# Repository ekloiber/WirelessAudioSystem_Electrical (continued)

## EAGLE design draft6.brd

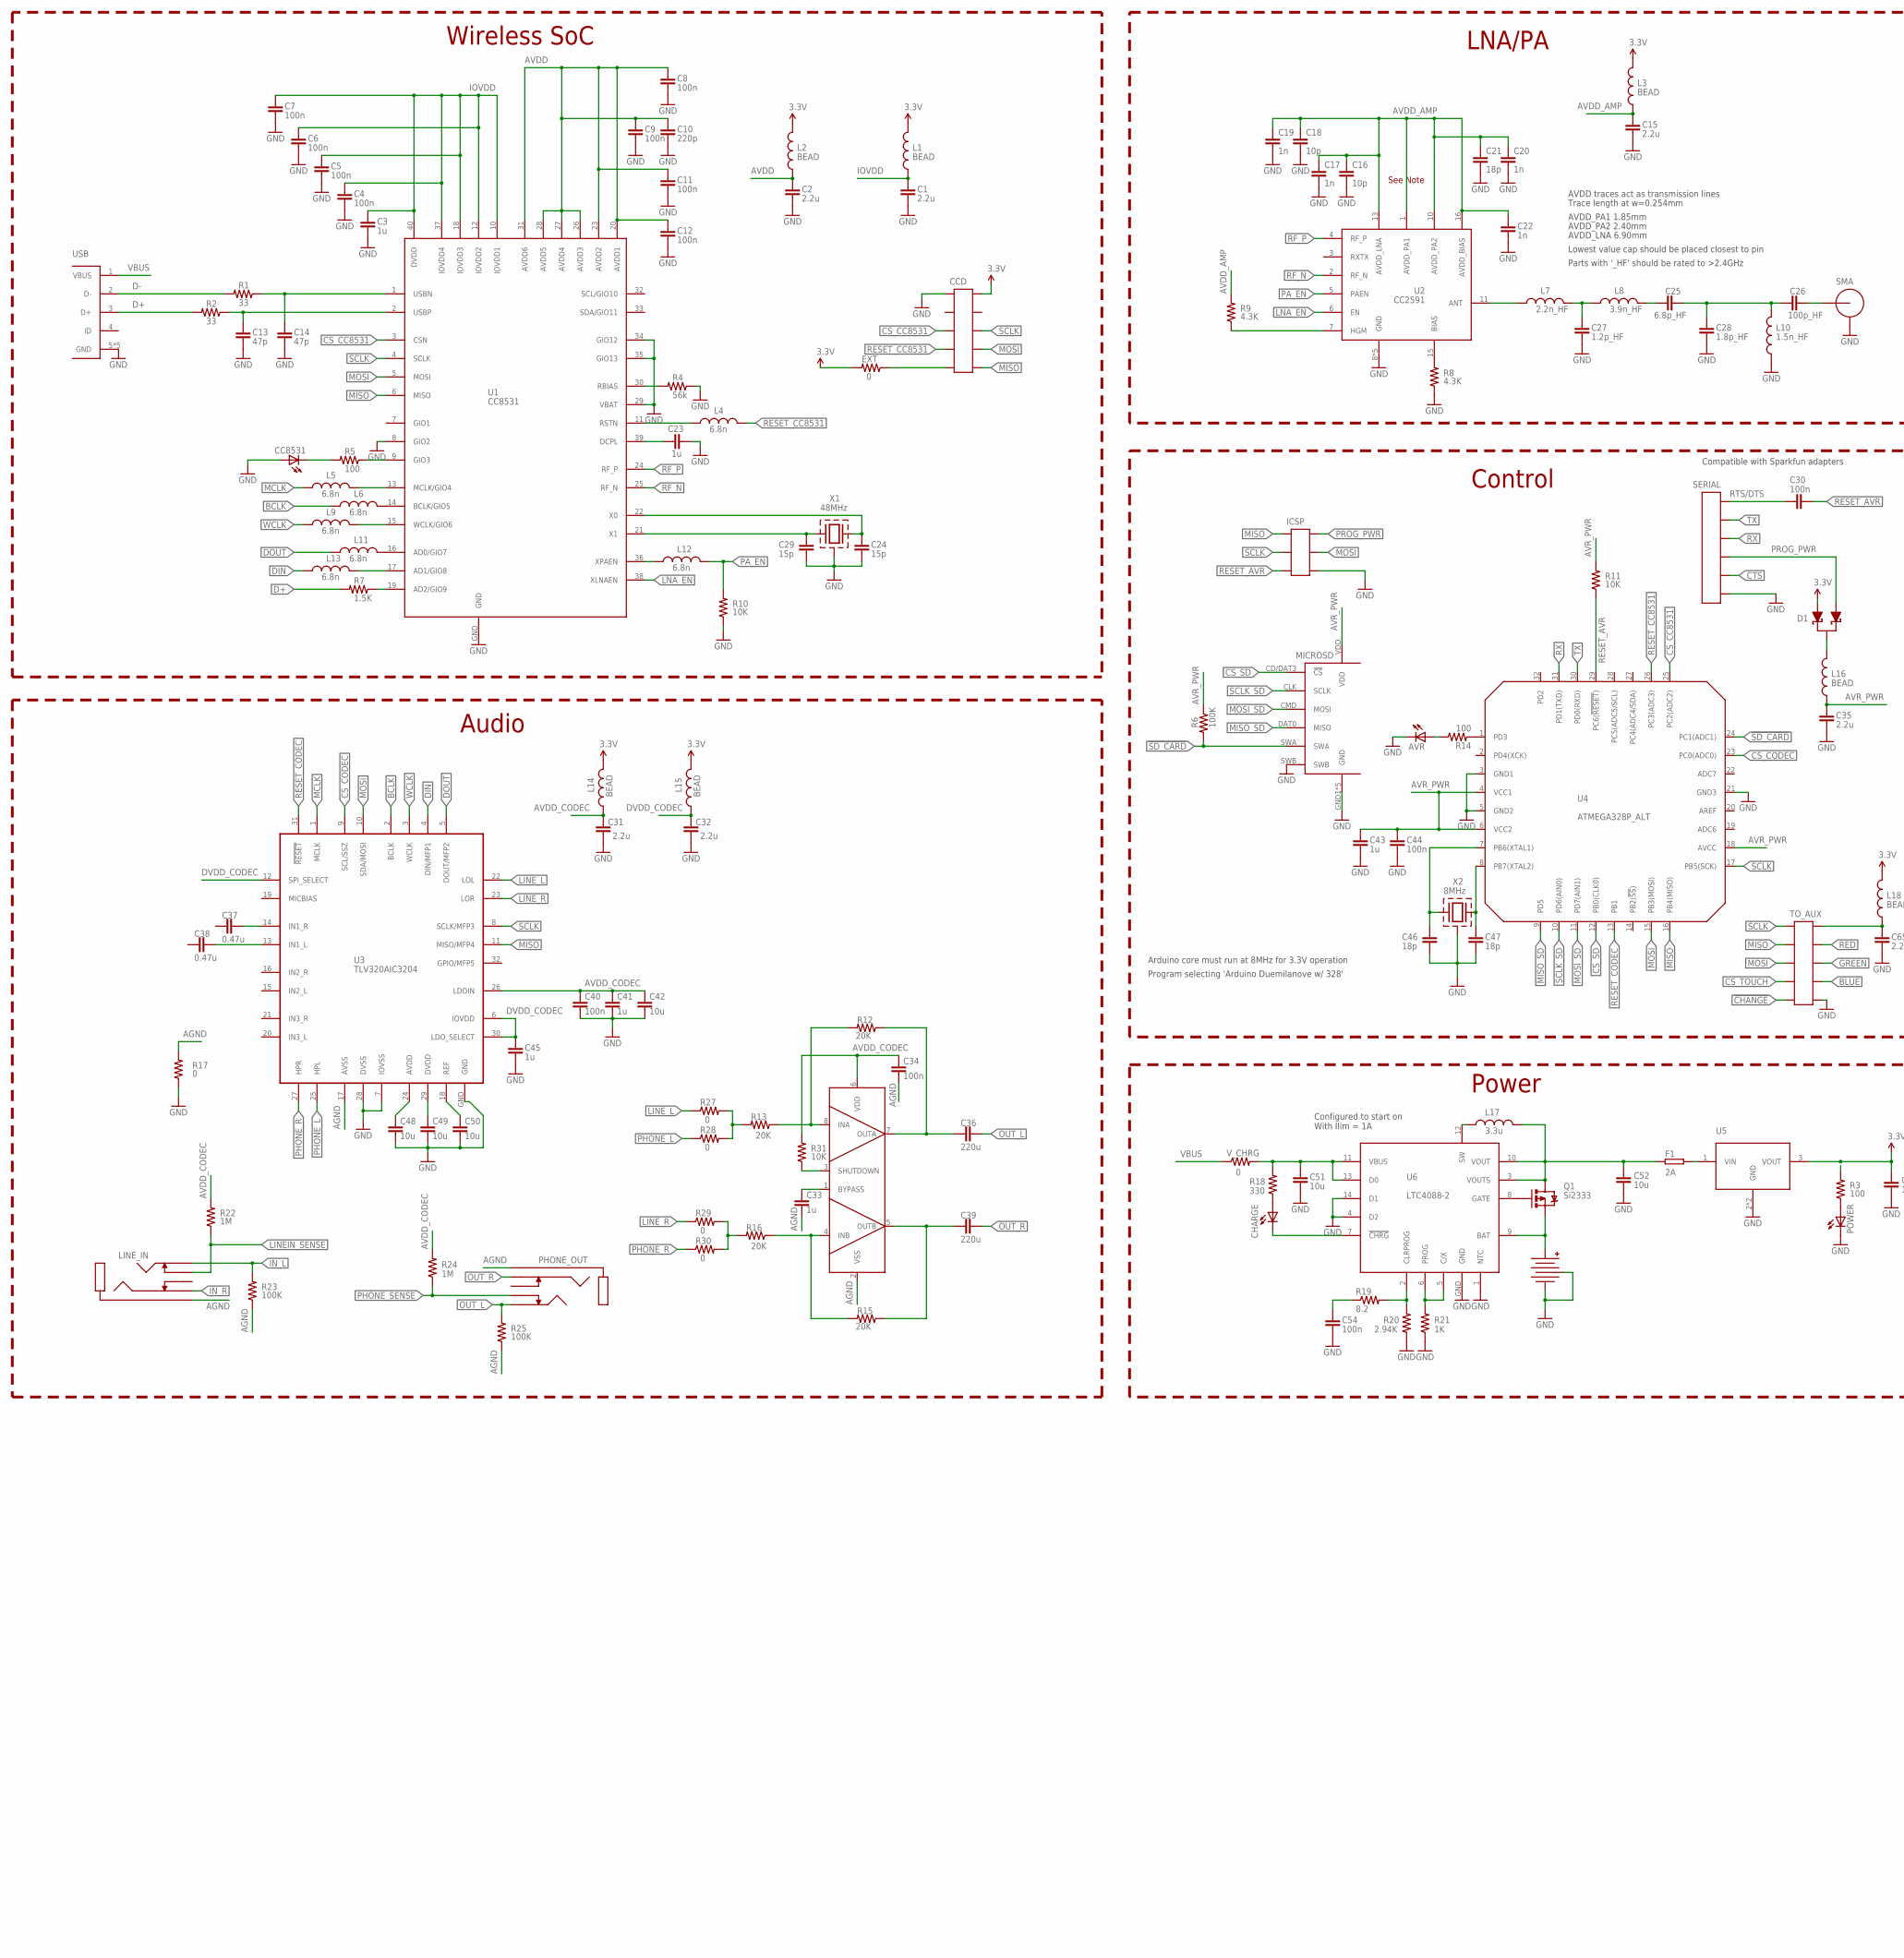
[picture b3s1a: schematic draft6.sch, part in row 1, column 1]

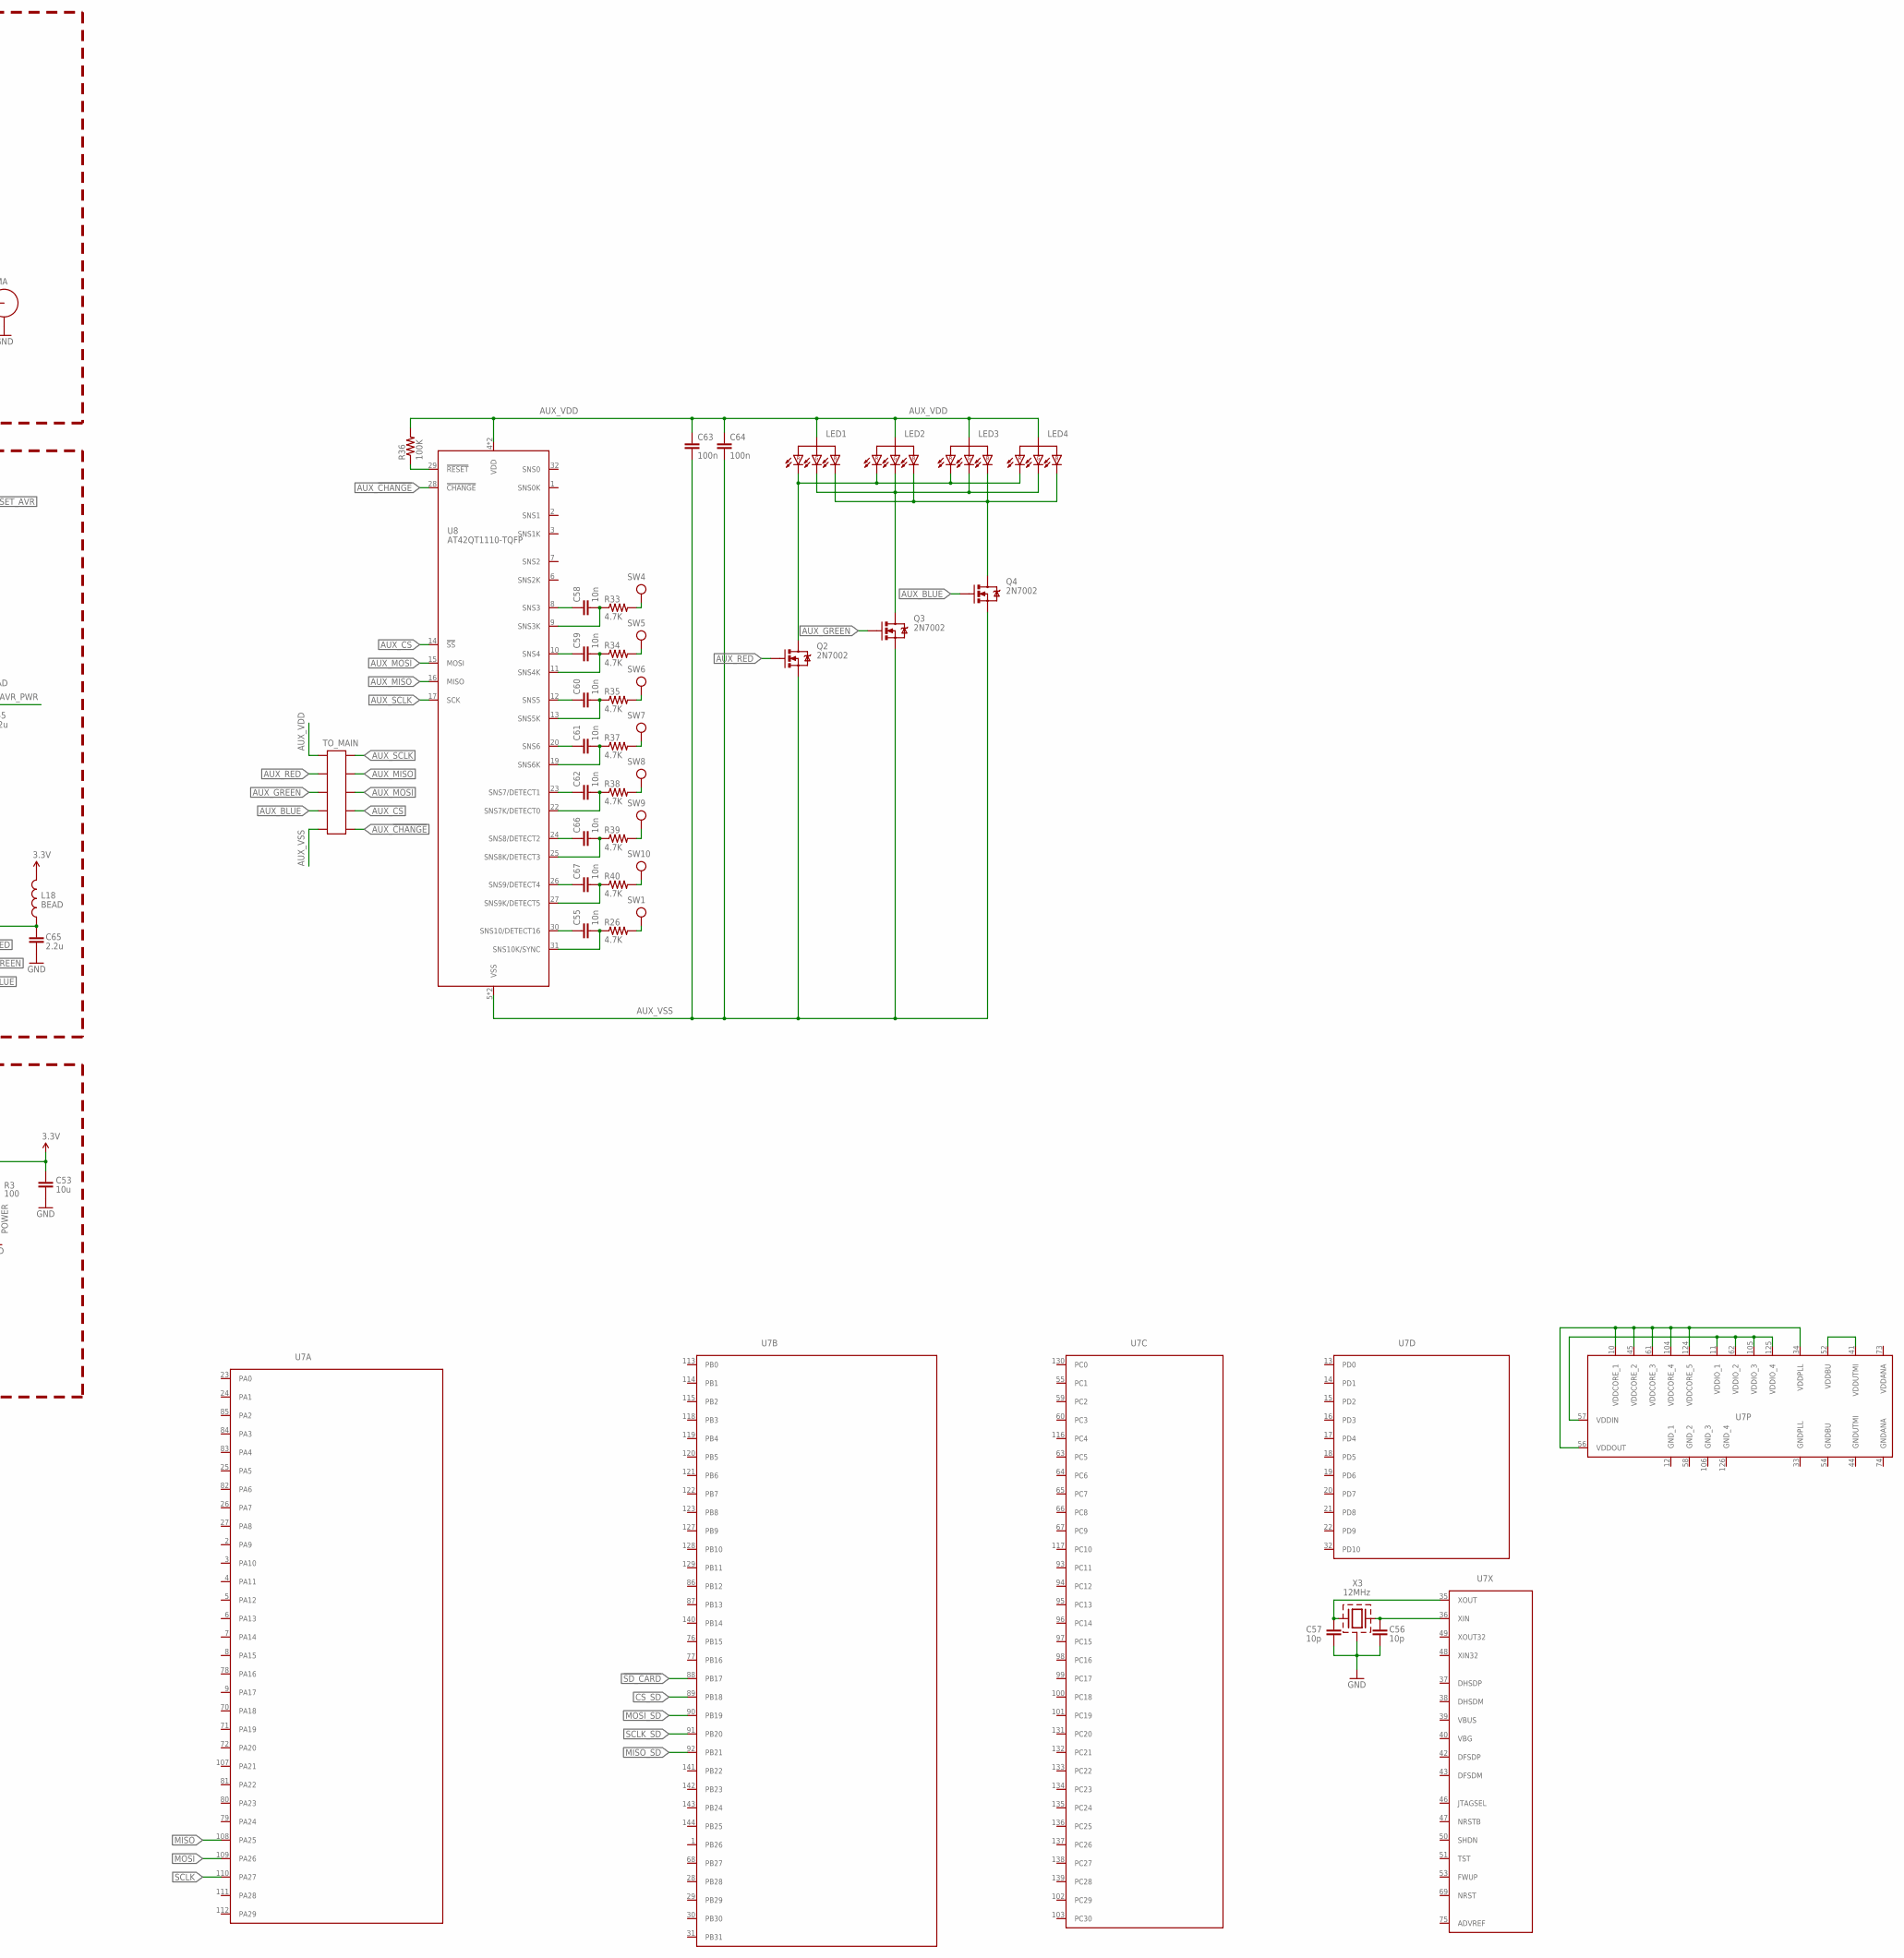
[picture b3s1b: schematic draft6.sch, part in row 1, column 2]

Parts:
AVR: LED1206; LED-1206
B1: BATTERY-LIPO-JST; 1775469-2
C1, C2, C15, C31, C32, C35, C65: 2.2u; C0603
C3, C23, C33, C41, C43, C45: 1u; C0603
C4, C5, C6, C7, C8, C9, C11, C12, C30, C34, C40, C44, C54, C63, C64: 100n; C0603
C10: 220p; C0603
C13, C14: 47p; C0603
C16, C18, C56, C57: 10p; C0603
C17, C19, C20, C22: 1n; C0603
C21, C46, C47: 18p; C0603
C24, C29: 15p; C0603
C25: 6.8p_HF; C0603
C26: 100p_HF; C0603
C27: 1.2p_HF; C0603
C28: 1.8p_HF; C0603
C36, C39: 220u; C1210
C37, C38: 0.47u; C0603
C42, C48, C49, C50, C51, C52, C53: 10u; C0603
C55, C58, C59, C60, C61, C62, C66, C67: 10n; C0603
CC8531: LED1206; LED-1206
CCD: HEADER-10P-SMD-MALE2; HEADER-10P-1.27MM
CHARGE: LED1206; LED-1206
D1: DUAL_SCHOTTKY; SOT-23
EXT: 0; R0603
F1: 2A; 1210
ICSP: HEADER-6P-SMD-1.27MM; HEADER-6P-1.27MM
L1, L2, L3, L14, L15, L16, L18: BEAD; 0603
L4, L5, L6, L9, L11, L12, L13: 6.8n; 0603
L7: 2.2n_HF; 0603
L8: 3.9n_HF; 0603
L10: 1.5n_HF; 0603
L17: 3.3u; IFSC-1111AB-01
LED1, LED2, LED3, LED4: LED_RGB; PLCC-4
LINE_IN: PHONE_SW-STX-35332-5N; STX-35332-5N
MICROSD: MICROSD104031-0811; MOLEX_104031-0811
PHONE_OUT: PHONE_SW-STX-35332-5N; STX-35332-5N
POWER: LED1206; LED-1206
Q1: Si2333; SOT23-3
Q2, Q3, Q4: 2N7002; SOT23-3
R1, R2: 33; R0603
R3, R5, R14: 100; R0603
R4: 56k; R0603
R6, R23, R25, R36: 100K; R0603
R7: 1.5K; R0603
R8, R9: 4.3K; R0603
R10, R11, R31: 10K; R0603
R12, R13, R15, R16: 20K; R0603
R17, R27, R28, R29, R30: 0; R0603
R18: 330; R0603
R19: 8.2; R0603
R20: 2.94K; R0603
R21: 1K; R0603
R22, R24: 1M; R0603
R26, R33, R34, R35, R37, R38, R39, R40: 4.7K; R0603
SERIAL: HEADER-6X1-961106-5500; HEADER-3M-961-6P-2.54MM
SMA: SMA-REVSMA-0.62; CONREVSMA003.062
SW1, SW4, SW5, SW6, SW7, SW8, SW9, SW10: TOUCH_PAD-CIRCLE-15MM; TOUCH-CIRCLE-15MM
TO_AUX: HEADER-10P-SMD-2MM-FEMALE; M22-63405
TO_MAIN: HEADER-10P-SMD-2MM-MALE; M22-53205
U1: CC8531; S-PVQFN-N40
U2: CC2591; S-PVQFN-N16
U3: TLV320AIC3204; S-PVQFN-N32
U4: ATMEGA328P_ALT; S-PQFP-N32
U5: MCP1826-SOT223; SOT-223
U6: LTC4088-2; DFN-14
U7: ATSAM3X8E_ALT-LQFP-144; LQFP-144
U8: AT42QT1110-TQFP; S-PQFP-N32
U$15: LM4881; SO08
USB: USB_MICRO_AB
V_CHRG: 0; R0603
X1: 48MHz; ABM3C
X2: 8MHz; ABM3B
X3: 12MHz; ABM8G

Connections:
3.3V: C53.1, CCD.2, D1.1 (A1), EXT.2, L1.2, L2.2, L3.2, L14.2, L15.2, L18.2, R3.2, U5.3 (VOUT)
!CHANGE: TO_AUX.9
!SD_CARD: MICROSD.SWA, R6.2, U4.24 (PC1(ADC1)), U7.88 (PB17)
AGND: C33.2, C34.2, LINE_IN.5 (GND), PHONE_OUT.5 (GND), R17.2, R23.1, R25.1, U3.17 (AVSS), U$15.2 (VSS)
AUX_!CHANGE: TO_MAIN.10, U8.28 (!CHANGE)
AUX_BLUE: Q4.1 (G), TO_MAIN.7
AUX_CS: TO_MAIN.8, U8.14 (!SS)
AUX_GREEN: Q3.1 (G), TO_MAIN.5
AUX_MISO: TO_MAIN.4, U8.16 (MISO)
AUX_MOSI: TO_MAIN.6, U8.15 (MOSI)
AUX_RED: Q2.1 (G), TO_MAIN.3
AUX_SCLK: TO_MAIN.2, U8.17 (SCK)
AUX_VDD: C63.1, C64.1, LED1.2 (A), LED1.2-2 (A), LED2.2 (A), LED2.2-2 (A), LED3.2 (A), LED3.2-2 (A), LED4.2 (A), LED4.2-2 (A), R36.2, TO_MAIN.1, U8.4 (VDD), U8.18 (VDD)
AUX_VSS: C63.2, C64.2, Q2.2 (S), Q3.2 (S), Q4.2 (S), TO_MAIN.9, U8.5 (VSS), U8.21 (VSS)
AVDD: C2.1, C8.1, C9.1, C10.1, C11.1, C12.1, L2.1, U1.20 (AVDD1), U1.23 (AVDD2), U1.26 (AVDD3), U1.27 (AVDD4), U1.28 (AVDD5), U1.31 (AVDD6)
AVDD_AMP: C15.1, C16.1, C17.1, C18.1, C19.1, C20.1, C21.1, C22.1, L3.1, R9.2, U2.1 (AVDD_PA1), U2.10 (AVDD_PA2), U2.13 (AVDD_LNA), U2.16 (AVDD_BIAS)
AVDD_CODEC: C31.1, C34.1, C40.1, C41.1, C42.1, L14.1, R22.2, R24.2, R31.2, U3.26 (LDOIN), U$15.6 (VDD)
AVR_PWR: C35.1, C43.1, C44.1, L16.1, MICROSD.VDD, R6.1, R11.2, U4.4 (VCC1), U4.6 (VCC2), U4.18 (AVCC)
BAT: B1.+, Q1.2 (S), U6.9 (BAT)
BCLK: L6.1, U3.2 (BCLK)
BLUE: TO_AUX.8
CS_CC8531: CCD.5, U1.3 (CSN), U4.25 (PC2(ADC2))
CS_CODEC: U3.9 (SCL/SSZ), U4.23 (PC0(ADC0))
CS_SD: MICROSD.CD/DAT3 (!CS), U4.12 (PB0(CLK0)), U7.89 (PB18)
CS_TOUCH: TO_AUX.7
CTS: SERIAL.2
D+: R2.2, R7.2, USB.3 (D+)
D-: R1.2, USB.2 (D-)
DIN: L13.1, U3.4 (DIN/MFP1)
DOUT: L11.1, U3.5 (DOUT/MFP2)
DVDD: C49.1, U3.29 (DVDD)
DVDD_CODEC: C32.1, C45.1, L15.1, U3.6 (IOVDD), U3.12 (SPI_SELECT), U3.30 (LDO_SELECT)
GND: AVR.C, B1.- (N), B1.X1 (CASE), B1.X2 (CASE), C1.2, C2.2, C3.2, C4.2, C5.2, C6.2, C7.2, C8.2, C9.2, C10.2, C11.2, C12.2, C13.2, C14.2, C15.2, C16.2, C17.2, C18.2, C19.2, C20.2, C21.2, C22.2, C23.2, C24.2, C27.2, C28.2, C29.2, C31.2, C32.2, C35.2, C40.2, C41.2, C42.2, C43.2, C44.2, C45.2, C46.2, C47.2, C48.2, C49.2, C50.2, C51.2, C52.2, C53.2, C54.2, C56.2, C57.2, C65.2, CC8531.A, CCD.1, ICSP.6, L10.1, MICROSD.GND1 (GND), MICROSD.GND2 (GND), MICROSD.GND3 (GND), MICROSD.GND4 (GND), MICROSD.SWB, MICROSD.VSS (GND), POWER.C, R4.1, R8.1, R10.1, R17.1, R20.1, R21.1, SERIAL.1, SMA.GND1 (GND), SMA.GND2 (GND), SMA.GND3 (GND), SMA.GND4 (GND), TO_AUX.10, U1.8 (GIO2), U1.29 (VBAT), U1.34 (GIO12), U1.35 (GIO13), U1.GND, U2.8 (GND), U2.9 (GND), U2.12 (GND), U2.14 (GND), U2.GND, U3.7 (IOVSS), U3.28 (DVSS), U3.GND, U4.3 (GND1), U4.5 (GND2), U4.21 (GND3), U5.2 (GND), U5.4 (GND), U6.1 (NTC), U6.4 (D2), U6.14 (D1), U6.GND, USB.5 (GND), USB.GND1 (GND), USB.GND2 (GND), USB.GND3 (GND), USB.GND4 (GND), X1.2 (CASE), X1.4 (CASE), X2.2 (CASE), X2.4 (CASE), X3.GND-1 (CASE), X3.GND-2 (CASE)
GREEN: TO_AUX.6
IN_L: LINE_IN.4 (L), R23.2
IN_R: LINE_IN.1 (R)
IOVDD: C1.1, C3.1, C4.1, C5.1, C6.1, C7.1, L1.1, U1.10 (IOVDD1), U1.12 (IOVDD2), U1.18 (IOVDD3), U1.37 (IOVDD4), U1.40 (DVDD)
IOVDD1: C14.1, R1.1, U1.1 (USBN)
IOVDD2: C13.1, R2.1, U1.2 (USBP)
LINEIN_SENSE: LINE_IN.3 (L_SW), R22.1
LINE_L: R27.1, U3.22 (LOL)
LINE_R: R29.1, U3.23 (LOR)
LNA_EN: U1.38 (XLNAEN), U2.6 (EN)
MCLK: L5.1, U3.1 (MCLK)
MISO: CCD.10, ICSP.1, TO_AUX.3, U1.6 (MISO), U3.11 (MISO/MFP4), U4.16 (PB4(MISO)), U7.108 (PA25)
MISO_SD: MICROSD.DAT0 (MISO), U4.9 (PD5), U7.92 (PB21)
MOSI: CCD.8, ICSP.4, TO_AUX.5, U1.5 (MOSI), U3.10 (SDA/MOSI), U4.15 (PB3(MOSI)), U7.109 (PA26)
MOSI_SD: MICROSD.CMD (MOSI), U4.11 (PD7(AIN1)), U7.90 (PB19)
unnamed: C29.1, U1.21 (X1), X1.1
unnamed: C24.1, U1.22 (X0), X1.3 (2)
unnamed: L4.1, U1.11 (RSTN)
unnamed: L11.2, U1.16 (AD0/GIO7)
unnamed: L6.2, U1.14 (BCLK/GIO5)
unnamed: D1.3 (C1), L16.2
unnamed: R8.2, U2.15 (BIAS)
unnamed: R9.1, U2.7 (HGM)
unnamed: C26.2, SMA.SIG
unnamed: C55.2, R26.1, U8.31 (SNS10K/SYNC)
unnamed: C55.1, U8.30 (SNS10/DETECT16)
unnamed: C46.1, U4.7 (PB6(XTAL1)), X2.1
unnamed: L7.1, U2.11 (ANT)
unnamed: C27.1, L7.2, L8.1
unnamed: C25.1, L8.2
unnamed: C25.2, C26.1, C28.1, L10.2
unnamed: C48.1, U3.24 (AVDD)
unnamed: L12.1, U1.36 (XPAEN)
unnamed: R4.2, U1.30 (RBIAS)
unnamed: C47.1, U4.8 (PB7(XTAL2)), X2.3 (2)
unnamed: C23.1, U1.39 (DCPL)
unnamed: F1.2, U5.1 (VIN)
unnamed: L5.2, U1.13 (MCLK/GIO4)
unnamed: R7.1, U1.19 (AD2/GIO9)
unnamed: L9.2, U1.15 (WCLK/GIO6)
unnamed: C33.1, U$15.1 (BYPASS)
unnamed: L13.2, U1.17 (AD1/GIO8)
unnamed: R5.1, U1.9 (GIO3)
unnamed: CC8531.C, R5.2
unnamed: C58.2, R33.1, U8.9 (SNS3K)
unnamed: POWER.A, R3.1
unnamed: CHARGE.C, U6.7 (!CHRG)
unnamed: CHARGE.A, R18.1
unnamed: C37.2, U3.14 (IN1_R)
unnamed: C38.2, U3.13 (IN1_L)
unnamed: L17.1, U6.12 (SW)
unnamed: R21.2, U6.5 (C/X), U6.6 (PROG)
unnamed: R19.2, R20.2, U6.2 (CLRPROG)
unnamed: C36.1, R12.1, U$15.7 (OUTA)
unnamed: C39.1, R15.1, U$15.5 (OUTB)
unnamed: C59.2, R34.1, U8.11 (SNS4K)
unnamed: C60.2, R35.1, U8.13 (SNS5K)
unnamed: R13.2, R27.2, R28.2
unnamed: R26.2, SW1.P$1
unnamed: R16.2, R29.2, R30.2
unnamed: R14.2, U4.1 (PD3)
unnamed: AVR.A, R14.1
unnamed: C54.1, R19.1
unnamed: C52.1, F1.1, L17.2, Q1.3 (D), U6.3 (VOUTS), U6.10 (VOUT)
unnamed: CCD.9, EXT.1
unnamed: Q1.1 (G), U6.8 (GATE)
unnamed: C51.1, R18.2, U6.11 (VBUS), U6.13 (D0), V_CHRG.2
unnamed: R12.2, R13.1, U$15.8 (INA)
unnamed: R15.2, R16.1, U$15.4 (INB)
unnamed: R31.1, U$15.3 (SHUTDOWN)
unnamed: U7.11 (VDDIO_1), U7.57 (VDDIN), U7.62 (VDDIO_2), U7.105 (VDDIO_3), U7.125 (VDDIO_4)
unnamed: U7.10 (VDDCORE_1), U7.34 (VDDPLL), U7.45 (VDDCORE_2), U7.56 (VDDOUT), U7.61 (VDDCORE_3), U7.104 (VDDCORE_4), U7.124 (VDDCORE_5)
unnamed: U7.41 (VDDUTMI), U7.52 (VDDBU)
unnamed: C56.1, U7.36 (XIN), X3.X2 (2)
unnamed: C58.1, U8.8 (SNS3)
unnamed: R33.2, SW4.P$1
unnamed: C59.1, U8.10 (SNS4)
unnamed: R34.2, SW5.P$1
unnamed: C60.1, U8.12 (SNS5)
unnamed: R35.2, SW6.P$1
unnamed: C66.2, R39.1, U8.25 (SNS8K/DETECT3)
unnamed: C65.1, L18.1, TO_AUX.2
unnamed: C67.2, R40.1, U8.27 (SNS9K/DETECT5)
unnamed: C66.1, U8.24 (SNS8/DETECT2)
unnamed: R39.2, SW9.P$1
unnamed: C61.2, R37.1, U8.19 (SNS6K)
unnamed: R37.2, SW7.P$1
unnamed: C62.2, R38.1, U8.22 (SNS7K/DETECT0)
unnamed: R38.2, SW8.P$1
unnamed: C62.1, U8.23 (SNS7/DETECT1)
unnamed: C61.1, U8.20 (SNS6)
unnamed: R36.1, U8.29 (!RESET)
unnamed: LED1.1 (KR), LED1.1-2 (KR), LED2.1 (KR), LED2.1-2 (KR), LED3.1 (KR), LED3.1-2 (KR), LED4.1 (KR), LED4.1-2 (KR), Q2.3 (D)
unnamed: LED1.4 (KG), LED1.4-2 (KG), LED2.4 (KG), LED2.4-2 (KG), LED3.4 (KG), LED3.4-2 (KG), LED4.4 (KG), LED4.4-2 (KG), Q3.3 (D)
unnamed: LED1.3 (KB), LED1.3-2 (KB), LED2.3 (KB), LED2.3-2 (KB), LED3.3 (KB), LED3.3-2 (KB), LED4.3 (KB), LED4.3-2 (KB), Q4.3 (D)
unnamed: C67.1, U8.26 (SNS9/DETECT4)
unnamed: R40.2, SW10.P$1
unnamed: C57.1, U7.35 (XOUT), X3.X1 (1)
OUT_L: C36.2, PHONE_OUT.4 (L), R25.2
OUT_R: C39.2, PHONE_OUT.1 (R)
PA_EN: L12.2, R10.2, U2.5 (PAEN)
PHONE_L: R28.1, U3.25 (HPL)
PHONE_R: R30.1, U3.27 (HPR)
PHONE_SENSE: PHONE_OUT.3 (L_SW), R24.1
PROG_PWR: D1.2 (A), ICSP.2, SERIAL.3
RED: TO_AUX.4
REF: C50.1, U3.18 (REF)
RESET_AVR: C30.2, ICSP.5, R11.1, U4.29 (PC6(!RESET!))
RESET_CC8531: CCD.7, L4.2, U4.26 (PC3(ADC3))
RESET_CODEC: U3.31 (!RESET), U4.13 (PB1)
RF_N: U1.25 (RF_N), U2.2 (RF_N)
RF_P: U1.24 (RF_P), U2.4 (RF_P)
RTS/DTS: C30.1, SERIAL.6
RX: SERIAL.4, U4.31 (PD1(TXD))
SCLK: CCD.6, ICSP.3, TO_AUX.1, U1.4 (SCLK), U3.8 (SCLK/MFP3), U4.17 (PB5(SCK)), U7.110 (PA27)
SCLK_SD: MICROSD.CLK (SCLK), U4.10 (PD6(AIN0)), U7.91 (PB20)
TX: SERIAL.5, U4.30 (PD0(RXD))
VBUS: USB.1 (VBUS), V_CHRG.1
WCLK: L9.1, U3.3 (WCLK)

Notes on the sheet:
See Note
Compatible with Sparkfun adapters
AVDD_PA1 1.85mm
AVDD_PA2 2.40mm
AVDD_LNA 6.90mm
Trace length at w=0.254mm
Configured to start on With Ilim = 1A
Audio
Power
Control
AVDD traces act as transmission lines
Lowest value cap should be placed closest to pin
Parts with '_HF' should be rated to >2.4GHz
Wireless SoC
LNA/PA
Arduino core must run at 8MHz for 3.3V operation
Program selecting 'Arduino Duemilanove w/ 328'

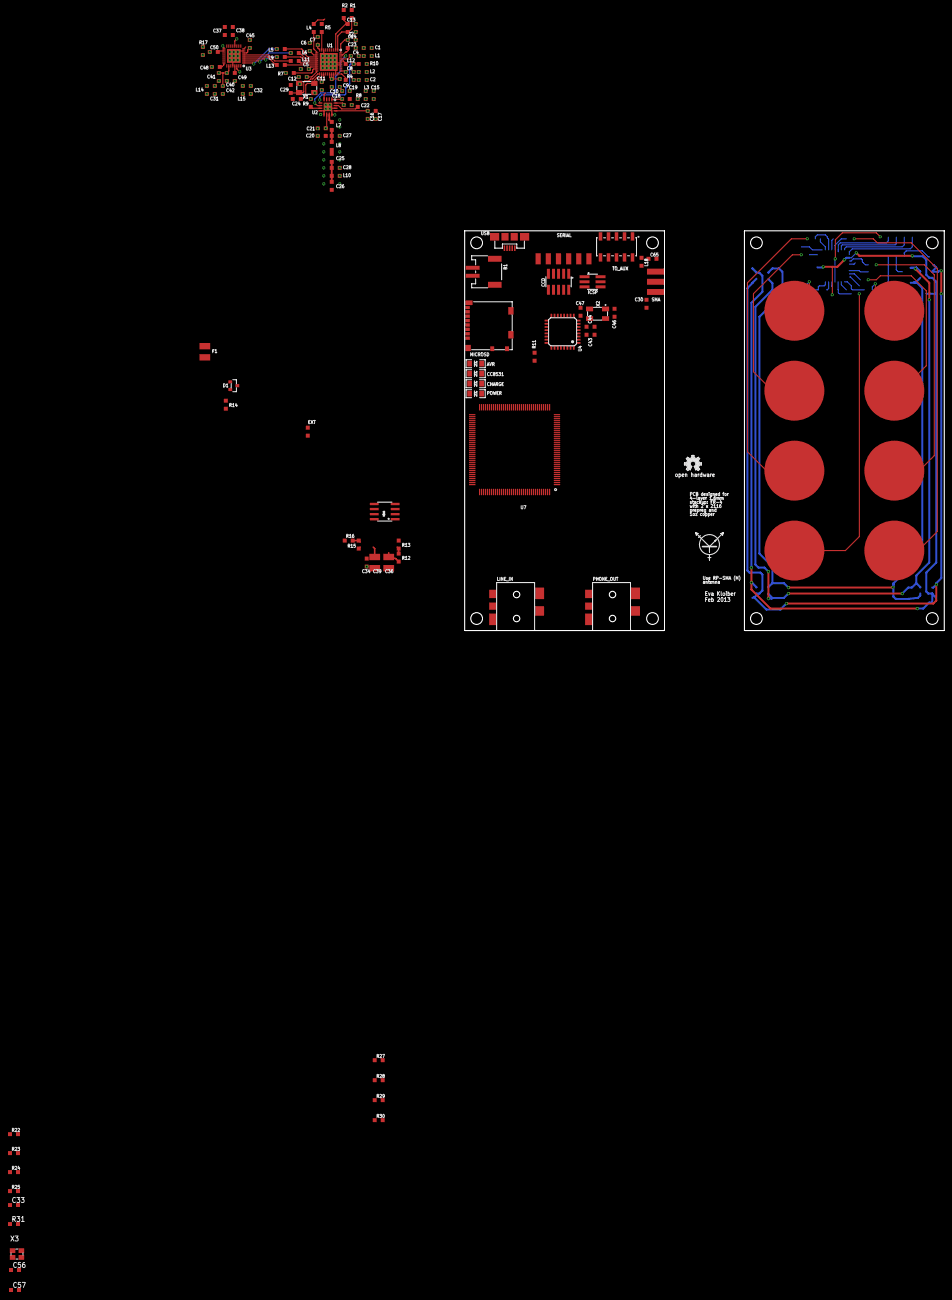
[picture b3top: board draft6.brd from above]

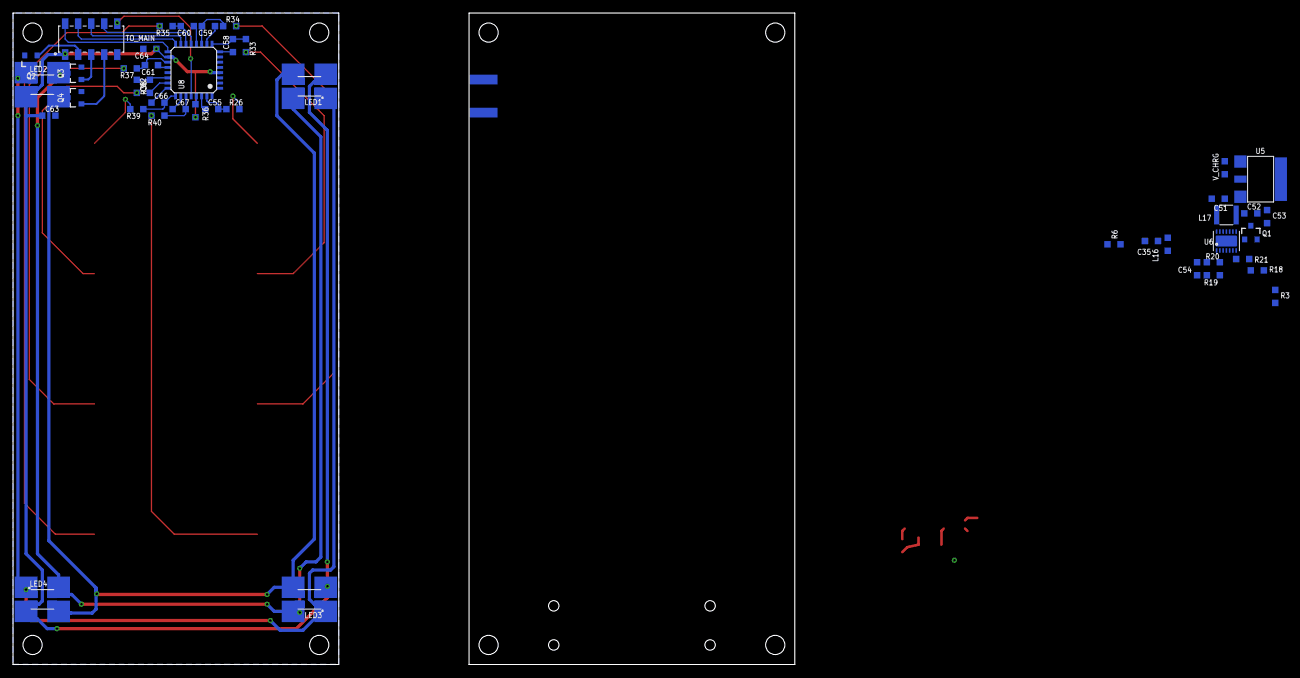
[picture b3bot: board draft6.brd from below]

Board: 4 copper layers, 120.0 x 100.0 mm, 185 parts (45 on the bottom side), 145 nets.

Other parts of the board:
U$1, U$5, U$6, U$7, U$8, U$11, U$12, U$13: STANDOFF_3/16
U$2, U$3: PHONE_PLUG
U$4, U$14: UBBP01
U$9: TRANS_SILK
U$10: OSHW_FILLX150_NOTEXT
